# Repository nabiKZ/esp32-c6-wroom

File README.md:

\# ESP32-C6 WROOM Board

Custom PCB based on ESP32-C6 module.

\## Features

\- WiFi 6 + BLE

\- Custom power supply

\- UART / Debug interface

\## Status

Prototype v1.0

\## Notes

Designed in KiCad

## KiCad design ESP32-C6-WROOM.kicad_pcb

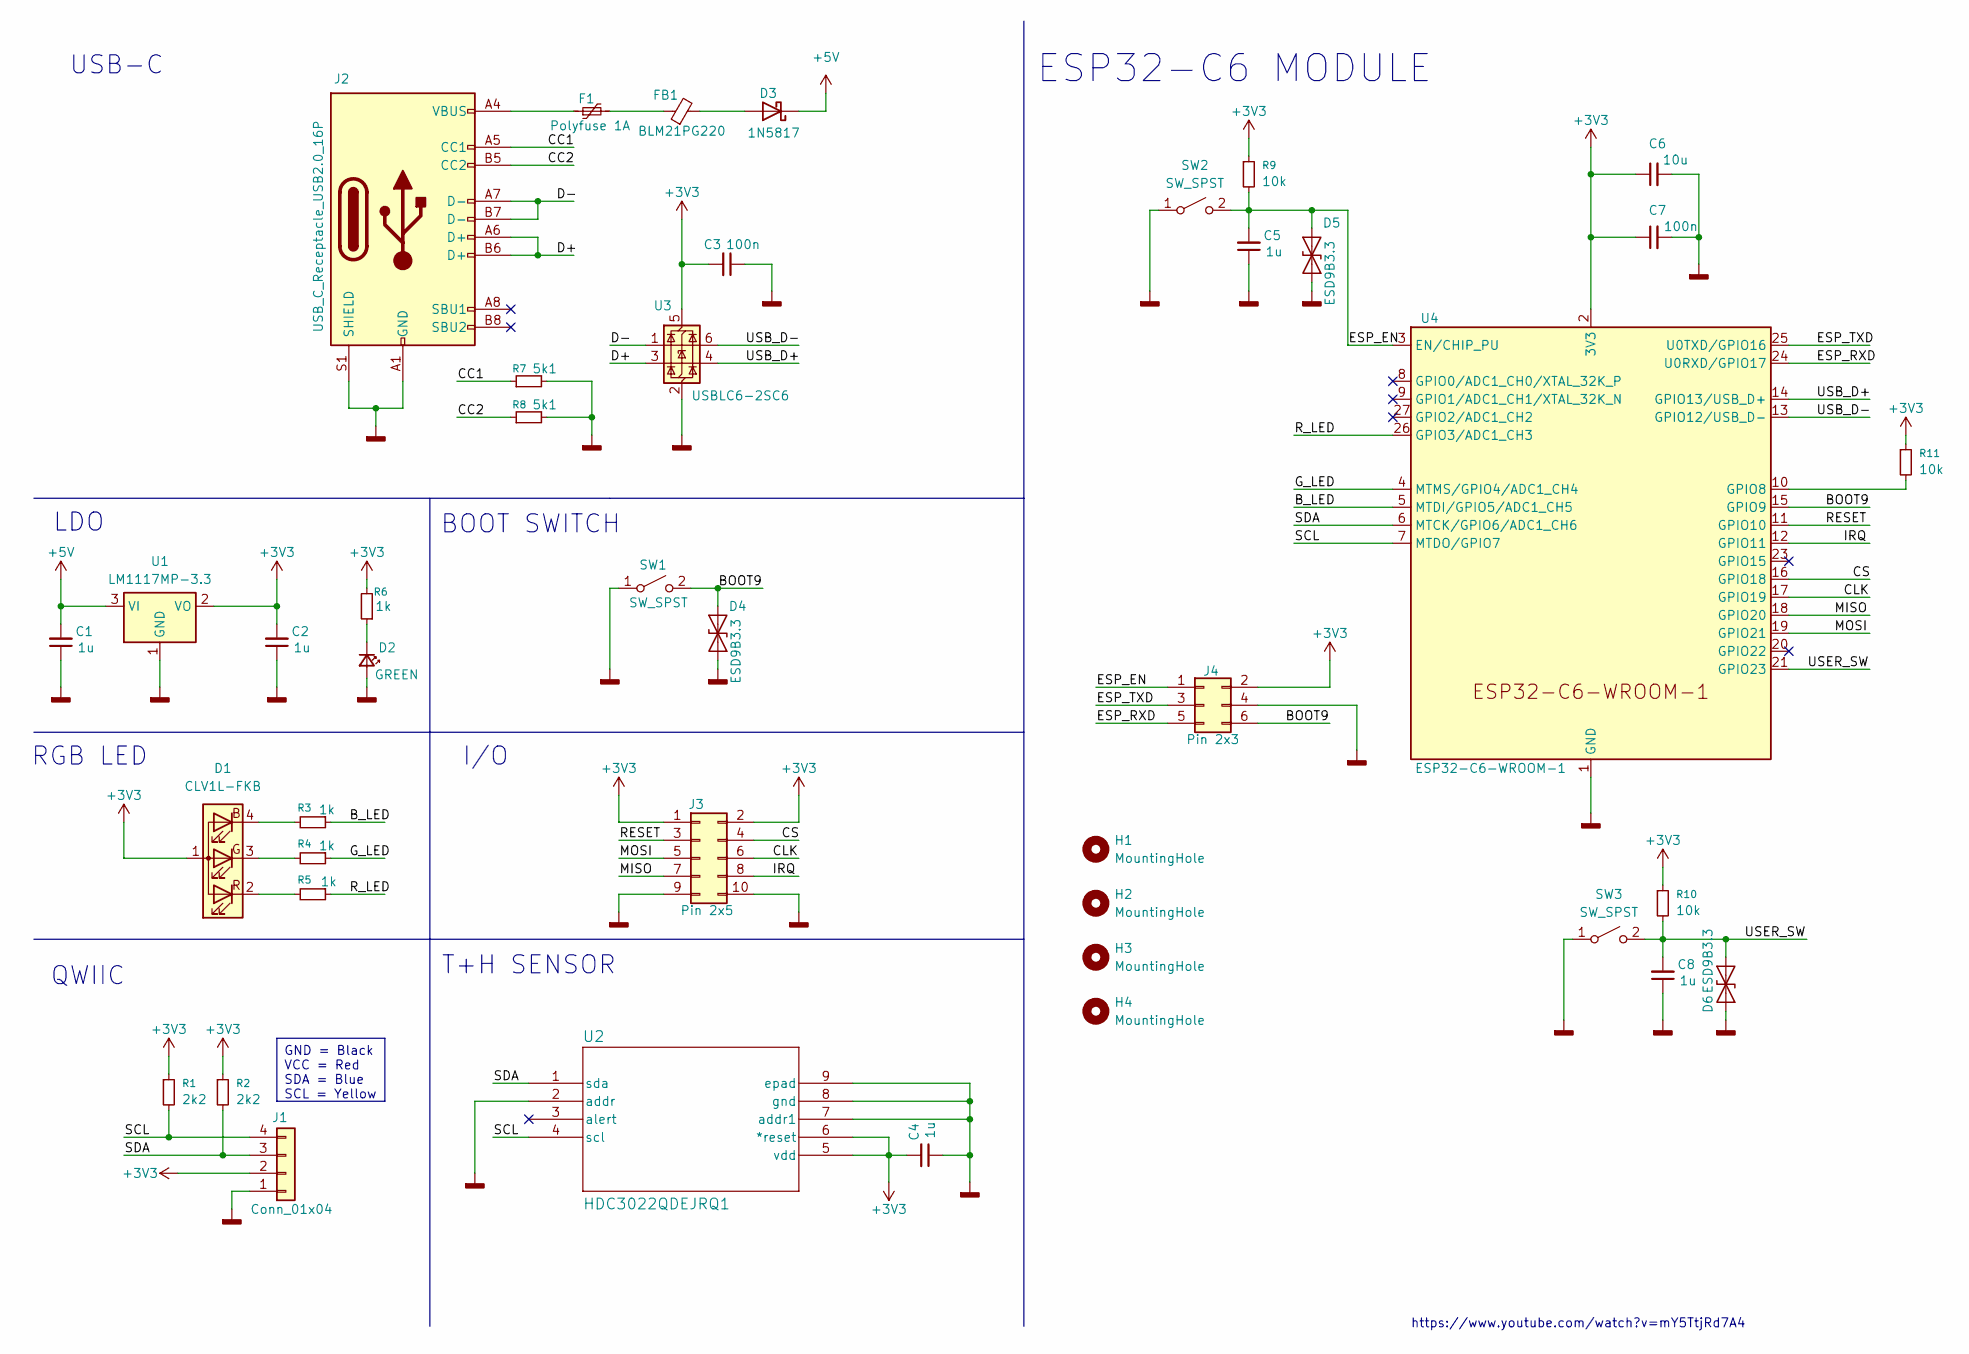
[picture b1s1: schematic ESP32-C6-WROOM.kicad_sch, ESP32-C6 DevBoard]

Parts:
C1, C2, C4, C5, C8: 1u; C_0402_1005Metric
C3, C7: 100n; C_0603_1608Metric
C6: 10u; C_0805_2012Metric
D1: CLV1L-FKB; LED_Cree-PLCC4_3.2x2.8mm_CCW
D2: GREEN; LED_0603_1608Metric
D3: 1N5817; D_SOD-123
D4, D5, D6: ESD9B3.3; D_SOD-923
F1: Polyfuse 1A; Fuse_1206_3216Metric
FB1: BLM21PG220; L_0805_2012Metric
H1, H2, H3, H4: MountingHole; MountingHole_3.2mm_M3_DIN965_Pad
J1: Conn_01x04; JST_SH_SM04B-SRSS-TB_1x04-1MP_P1.00mm_Horizontal
J2: USB_C_Receptacle_USB2.0_16P; USB_C_Receptacle_HRO_TYPE-C-31-M-12
J3: Pin 2x5; PinHeader_2x05_P2.54mm_Vertical
J4: Pin 2x3; PinHeader_2x03_P2.54mm_Vertical
R1, R2: 2k2; R_0402_1005Metric
R3, R4, R5, R6: 1k; R_0402_1005Metric
R7, R8: 5k1; R_0402_1005Metric
R9, R10, R11: 10k; R_0402_1005Metric
SW1, SW2: SW_SPST; SW_SPST_B3U-1000P
SW3: SW_SPST; SW_Tactile_SPST_Angled_PTS645Vx31-2LFS
U1: LM1117MP-3.3; SOT-223-3_TabPin2
U2: HDC3022QDEJRQ1; WSON8_DEJ_TEX
U3: USBLC6-2SC6; SOT-23-6
U4: ESP32-C6-WROOM-1

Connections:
+3V3: C2.2, C3.2, C4.2, C6.1, C7.1, D1.1 (A), J1.2, J3.1, J3.2, J4.2, R1.1, R2.1, R6.2, R9.1, R10.1, R11.1, U1.2 (VO), U2.5 (vdd), U2.6 (*reset), U3.5 (VBUS), U4.2 (3V3)
+5V: C1.2, D3.1 (K), U1.3 (VI)
/BOOT9: D4.2 (A2), J4.6, SW1.2 (B), U4.15 (GPIO9)
/B_LED: R3.1, U4.5 (MTDI/GPIO5/ADC1_CH5)
/CC1: J2.A5 (CC1), R7.1
/CC2: J2.B5 (CC2), R8.1
/CLK: J3.6, U4.17 (GPIO19)
/CS: J3.4, U4.16 (GPIO18)
/D+: J2.A6 (D+), J2.B6 (D+), U3.3 (I/O2)
/D-: J2.A7 (D-), J2.B7 (D-), U3.1 (I/O1)
/ESP_EN: C5.2, D5.2 (A2), J4.1, R9.2, SW2.2 (B), U4.3 (EN/CHIP_PU)
/ESP_RXD: J4.5, U4.24 (U0RXD/GPIO17)
/ESP_TXD: J4.3, U4.25 (U0TXD/GPIO16)
/G_LED: R4.1, U4.4 (MTMS/GPIO4/ADC1_CH4)
/IRQ: J3.8, U4.12 (GPIO11)
/MISO: J3.7, U4.18 (GPIO20)
/MOSI: J3.5, U4.19 (GPIO21)
/RESET: J3.3, U4.11 (GPIO10)
/R_LED: R5.1, U4.26 (GPIO3/ADC1_CH3)
/SCL: J1.4, R1.2, U2.4 (scl), U4.7 (MTDO/GPIO7)
/SDA: J1.3, R2.2, U2.1 (sda), U4.6 (MTCK/GPIO6/ADC1_CH6)
/USB_D+: U3.4 (I/O2), U4.14 (GPIO13/USB_D+)
/USB_D-: U3.6 (I/O1), U4.13 (GPIO12/USB_D-)
/USER_SW: C8.2, D6.2 (A2), R10.2, SW3.2 (B), U4.21 (GPIO23)
GNDD: C1.1, C2.1, C3.1, C4.1, C5.1, C6.2, C7.2, C8.1, D2.2 (A), D4.1 (A1), D5.1 (A1), D6.1 (A1), J1.1, J2.A1 (GND), J2.A12 (GND), J2.B1 (GND), J2.B12 (GND), J2.S1 (SHIELD), J3.9, J3.10, J4.4, R7.2, R8.2, SW1.1 (A), SW2.1 (A), SW3.1 (A), U1.1 (GND), U2.2 (addr), U2.7 (addr1), U2.8 (gnd), U2.9 (epad), U3.2 (GND), U4.1 (GND), U4.28 (GND), U4.29 (GND)
unnamed: D1.4 (BK), R3.2
unnamed: D1.3 (GK), R4.2
unnamed: D1.2 (RK), R5.2
unnamed: D2.1 (K), R6.1
unnamed: D3.2 (A), FB1.2
unnamed: F1.1, J2.A4 (VBUS), J2.A9 (VBUS), J2.B4 (VBUS), J2.B9 (VBUS)
unnamed: F1.2, FB1.1
unnamed: R11.2, U4.10 (GPIO8)

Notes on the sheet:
USB-C
I/O
ESP32-C6 MODULE
https://www.youtube.com/watch?v=mY5TtjRd7A4
QWIIC
T+H SENSOR
RGB LED
BOOT SWITCH
LDO
GND = Black VCC = Red SDA = Blue SCL = Yellow

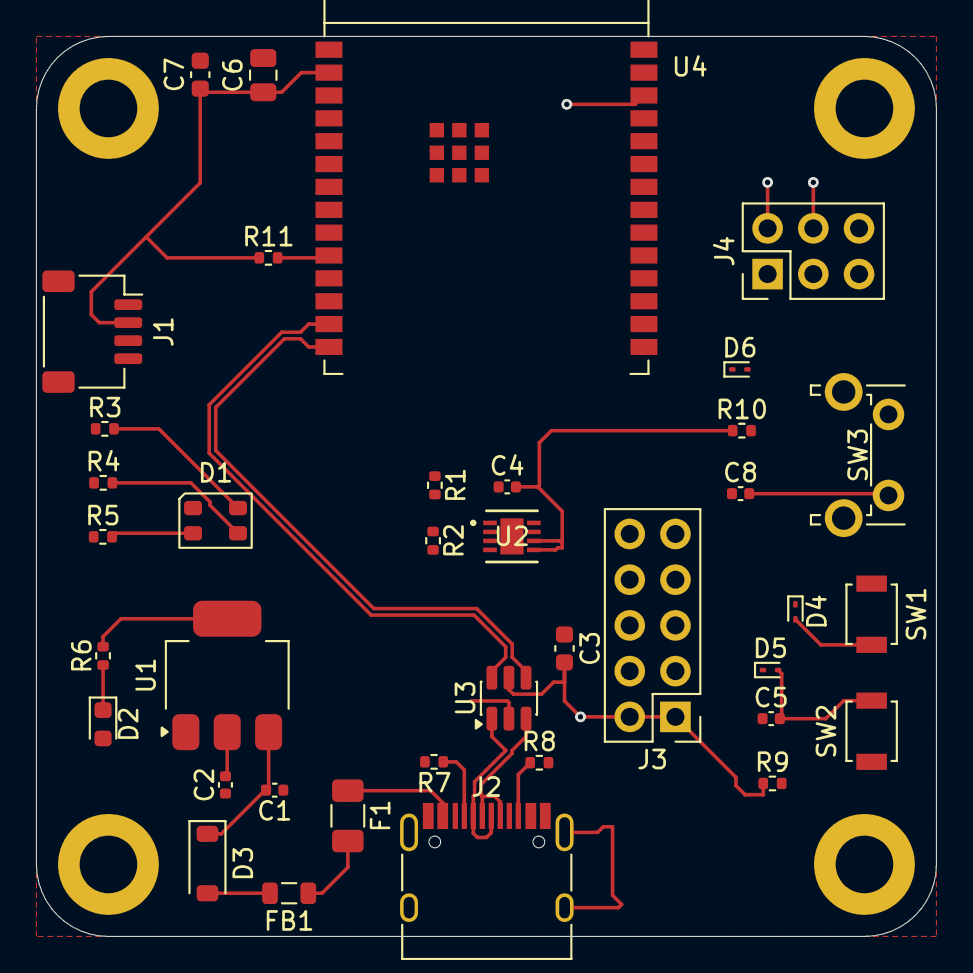
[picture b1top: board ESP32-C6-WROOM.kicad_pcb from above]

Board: 4 copper layers, 50.0 x 50.0 mm, 42 parts (0 on the bottom side), 33 nets.

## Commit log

2026-03-17 Install ESp32-C6 KiCad project
2026-03-17 Cleanup: remove KiCad temp and backup files
2026-03-17 Final cleanup
2026-03-17 Remove remaining temp files
2026-03-17 Add README
2026-03-17 трассировка дорожек
2026-03-17 auto backup
